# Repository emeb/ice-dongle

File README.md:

# ice-dongle
USB-C Dongle with ice40 UP5k FPGA

## Abstract
This is a small USB connected FPGA board in a "dongle" form-factor. Note that
it's not a true dongle since it doesn't have a USB plug (USB-C plugs are not
practical for DIY assembly at the time this was designed) - instead it has a
USB-C jack and you can use an inexpensive M-M adapter to achieve dongle-like
function.

For I/O it provides an 18-pin FPC connector that conforms to the Eye-SPI
standard found on some Adafruit products. This standard includes 3.3V power
as well as 16 GPIO for things like SPI or I2C device, most often TFT LCD
displays and user interfaces.

The FPGA is directly connected to USB and is pinned-out similarly to the
1bitsquared Icebreaker Bitsy so the NO2FPGA bootloader and user designs for
that ecosystem should port over with minimal changes. It includes 8MB of flash
and 8MB of PSRAM, as well as an RGB LED and a user button.

Initial programming of the FPGA bitstream takes place through a 1.27mm SMD
header footprint on the back of the board. The original intent was to access
this temporarily via the Adafruit "Pogo Pin Probe Clip" which should have
attached easily over the pads. Unfortunately the pogo pin row spacing is too
narrow for the SMT header pads so I ended up soldering on a header and using
a normal cable. This may be fixed in future revisions, but for now an actual
header + cable is probably more reliable for long-term development.

## Status
### 22-10-15
Boards are back from OSHpark and so far things are working.
* USB power, regulators and clock oscillator are running properly.
  * Minor silkscreen error was discovered - reference designators for R14 and C10 swapped.
* FPGA configures via programming header and from SPI flash.
* SPI flash can be written from the programming header.
* RGB LED works.
* EYESPI bus works with ST7789 TFT LCD
* PSRAM works.

### 22-10-16
USB FS interface is fully functional with the NO2 Bootloader. I've forked it to
add a custom BOARD target for ice-dongle but I'll submit a PR to the main project
when things settle down a bit. For the time being here's my fork:

[NO2 Bootloader](https://github.com/emeb/no2bootloader)

To build, clone that and follow the directions in the README. A few additional
notes:
* Don't forget to `git submodule update --init` to get all the related material
from the NO2 ecosystem.
* To build use `make BOARD=ice-dongle bootloader`
* The `riscv_lcd` gateware project has a `make dfu` target that shows how to use
the bootloader.

### 22-10-17
Ordered some helper boards to make interfacing easier:
* ice-fpc-pmod
* ice-prog-adapt

find out more about them in the [Hardware](Hardware) directory.

### 22-11-20
* Sylvain Munaut (@tnt) has built up a couple ice-dongle boards and confirmed that
they work outside my lab. He did spot another silkscreen error - R10 and C5 reference
designators are swapped. This doesn't significantly affect the board operation but
should be corrected.
* Updated NO2 board definition to put serial pins on programming
header and sent a PR which has been accepted. You can now use the mainline
NO2 bootloader repo instead of my fork.
* Added a LiteX gateware design. This works but even a minimal demo uses > 80% of
the FPGA resources.

### 22-11-21
Corrected silkscreen errors and bumped revision to V0.1a

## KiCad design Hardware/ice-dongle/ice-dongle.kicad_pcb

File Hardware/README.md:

# ice-dongle Hardware
These are kicad projects for the ice-dongle board.

## ice-dongle
the main board design for the ice-dongle

## ice-fpc-pmod
a simple FPC to dual PMOD breakout board. Note that this can be
used for both FPC -> PMOD socket as well as PMOD pin header -> FPC just by
flipping the board upside down.

## ice-prog-adapt
breaks out the 10-pin 1.27mm IDC header to 2.54mm single-row
pins for connection to a programmer and UART.

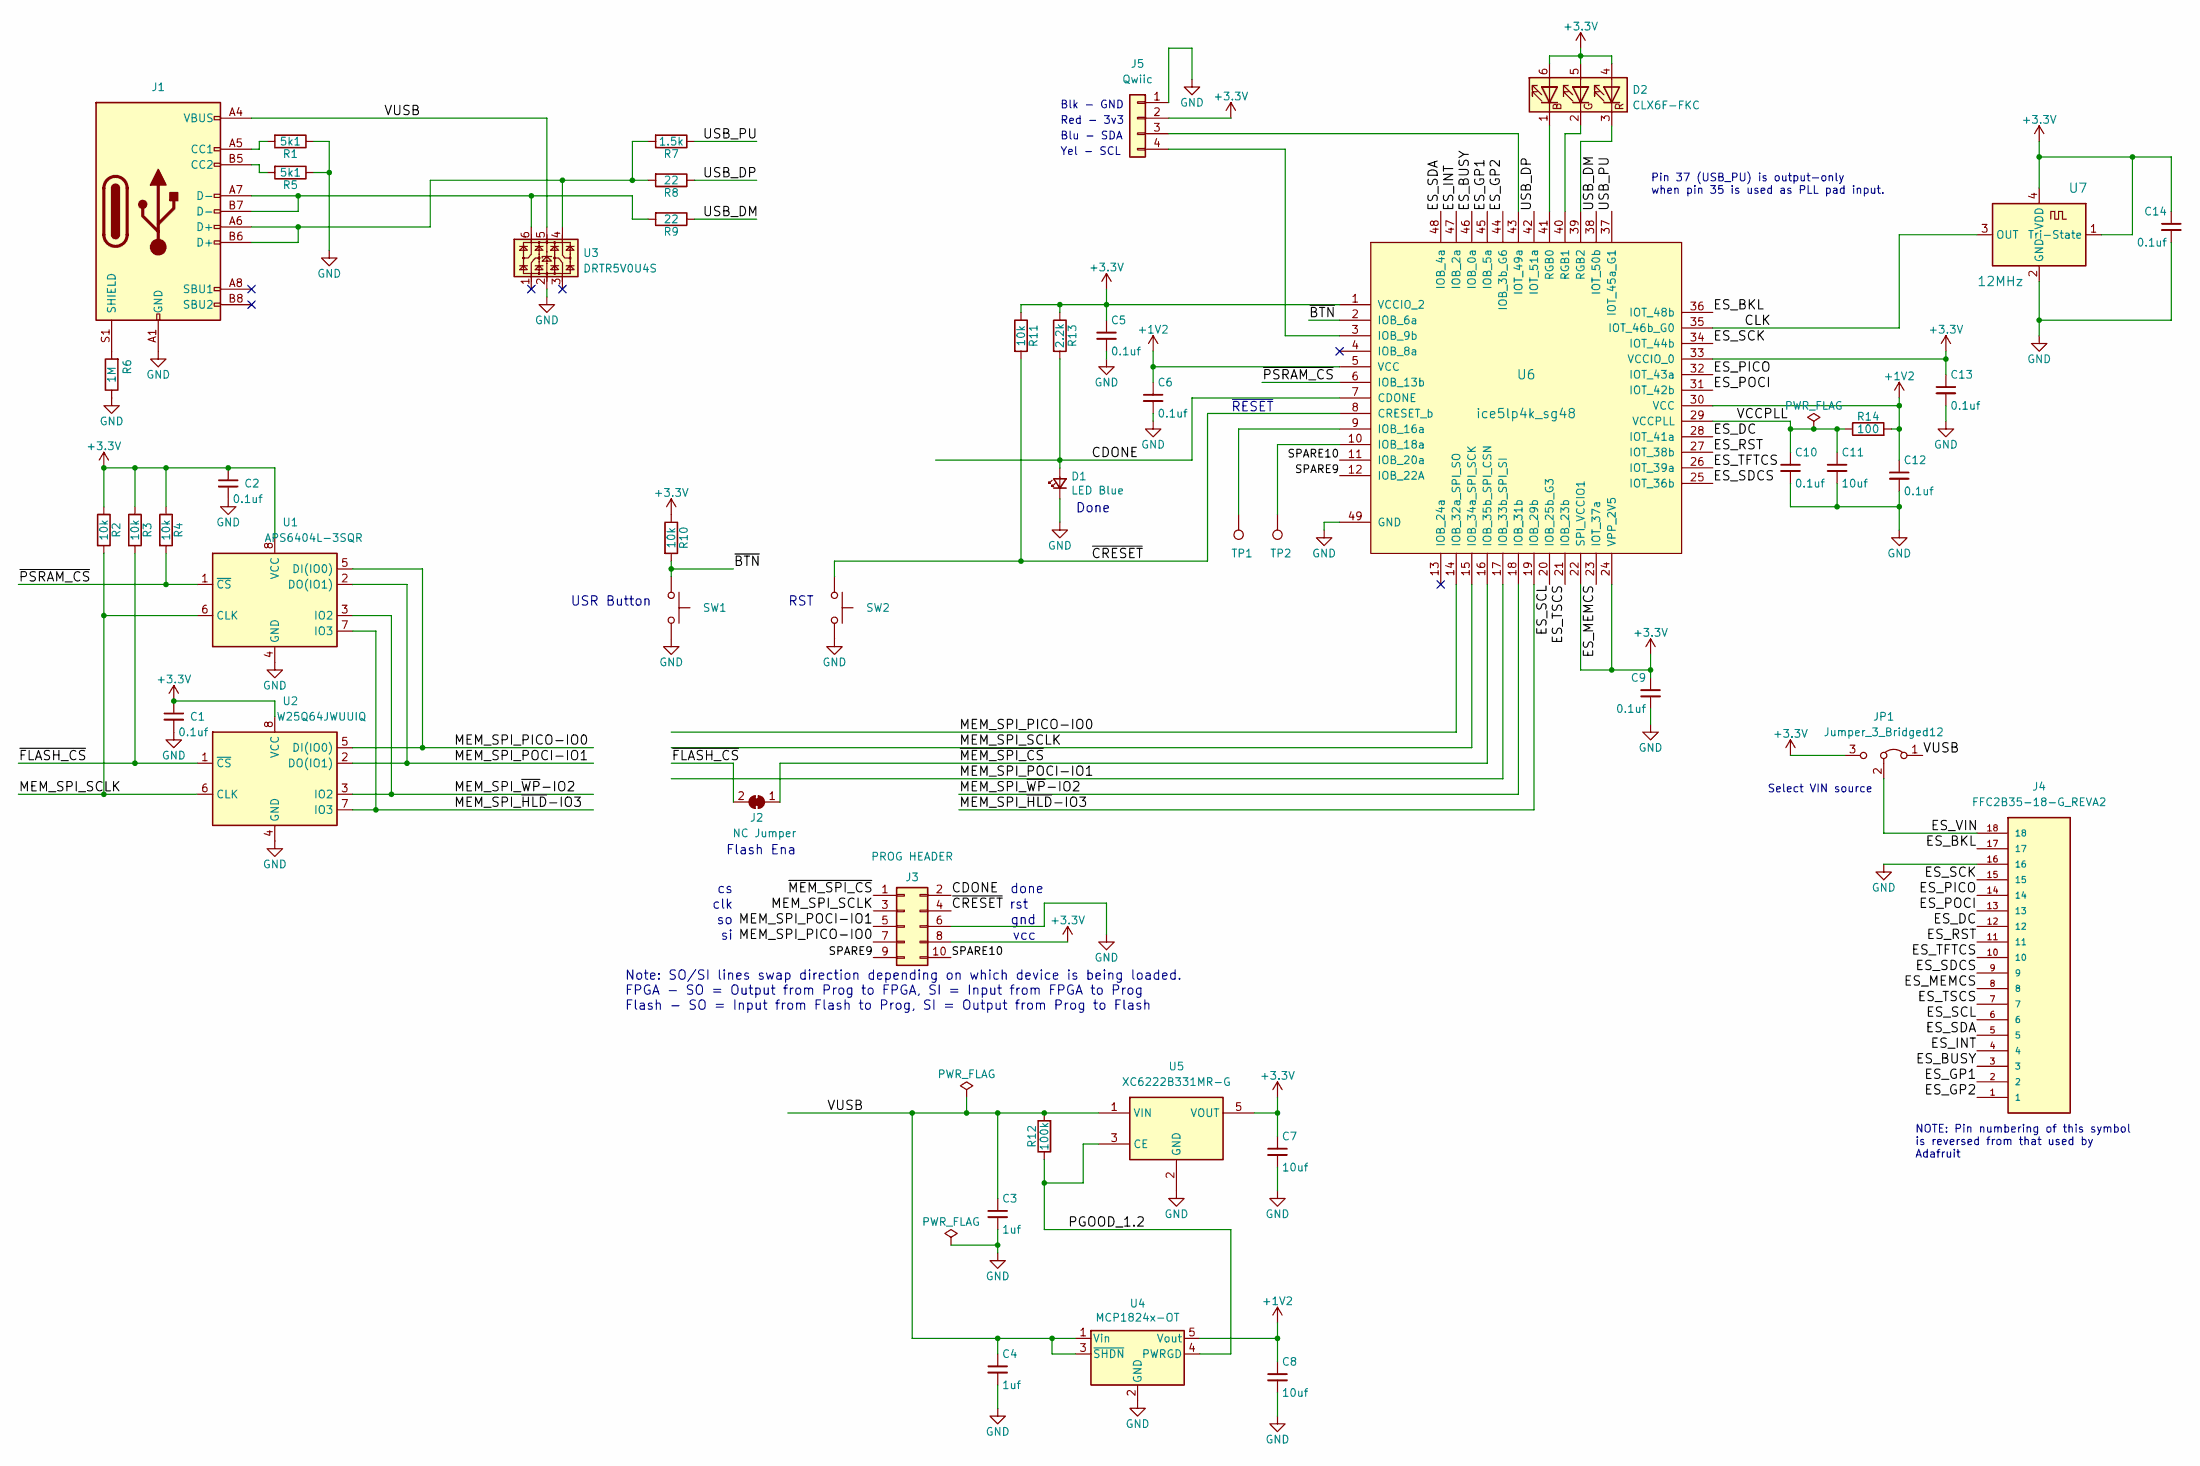
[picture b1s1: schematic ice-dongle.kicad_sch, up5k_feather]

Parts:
C1, C2, C5, C6, C9, C10, C12, C13, C14: 0.1uf; C_0402_1005Metric
C3, C4: 1uf; C_0402_1005Metric
C7, C8, C11: 10uf; C_0805_2012Metric
D1: LED Blue; LED_0603_1608Metric
D2: CLX6F-FKC; LED_RGB_PLCC-6
J1: USB_C_Receptacle_USB2.0; USB_C_Receptacle_HRO_TYPE-C-31-M-12
J2: NC Jumper; SolderJumper-2_P1.3mm_Bridged_RoundedPad1.0x1.5mm
J3: PROG HEADER; PinHeader_2x05_P1.27mm_Vertical_SMD
J4: FFC2B35-18-G_REVA2; GCT_FFC2B35-18-G_REVA2; PARTREV A2
J5: Qwiic; PinHeader_1x04_P1.27mm_Vertical
JP1: Jumper_3_Bridged12; SolderJumper-3_P1.3mm_Bridged12_RoundedPad1.0x1.5mm
R1, R5: 5k1; R_0402_1005Metric
R2, R3, R4, R10, R11: 10k; R_0402_1005Metric
R6: 1M; R_0402_1005Metric
R7: 1.5k; R_0402_1005Metric
R8, R9: 22; R_0402_1005Metric
R12: 100k; R_0402_1005Metric
R13: 2.2k; R_0402_1005Metric
R14: 100; R_0402_1005Metric
SW1, SW2: SW_Push; SW_SPST_PTS815
TP1, TP2: TestPoint; TestPoint_Pad_D0.5mm
U1: APS6404L-3SQR; USON-8_2x3
U2: W25Q64JWUUIQ; USON-8_4x3
U3: DRTR5V0U4S; SOT-363_SC-70-6
U4: MCP1824x-OT; SOT-23-5
U5: XC6222B331MR-G; SOT-23-5
U6: ice5lp4k_sg48; QFN-48-1EP_7x7mm_P0.5mm_EP5.3x5.3mm
U7: 12MHz; Oscillator_SMD_ECS_2520MV-xxx-xx-4Pin_2.5x2.0mm

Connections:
+1V2: C6.1, C8.1, C12.1, R14.2, U4.5 (Vout), U6.5 (VCC), U6.30 (VCC)
+3.3V: C1.1, C2.1, C5.1, C7.1, C9.1, C13.1, C14.1, D2.4 (BA), D2.5 (GA), D2.6 (RA), J3.8, J5.2, JP1.3 (B), R2.1, R3.1, R4.1, R10.1, R11.1, R13.1, U1.8 (VCC), U2.8 (VCC), U5.5 (VOUT), U6.1 (VCCIO_2), U6.22 (SPI_VCCIO1), U6.24 (VPP_2V5), U6.33 (VCCIO_0), U7.1 (Tri-State), U7.4 (VDD)
/CDONE: D1.2 (A), J3.2, R13.2, U6.7 (CDONE)
/CLK: U6.35 (IOT_46b_G0), U7.3 (OUT)
/ES_BKL: J4.17, U6.36 (IOT_48b)
/ES_BUSY: J4.3, U6.46 (IOB_0a)
/ES_DC: J4.12, U6.28 (IOT_41a)
/ES_GP1: J4.2, U6.45 (IOB_5a)
/ES_GP2: J4.1, U6.44 (IOB_3b_G6)
/ES_INT: J4.4, U6.47 (IOB_2a)
/ES_MEMCS: J4.8, U6.23 (IOT_37a)
/ES_PICO: J4.14, U6.32 (IOT_43a)
/ES_POCI: J4.13, U6.31 (IOT_42b)
/ES_RST: J4.11, U6.27 (IOT_38b)
/ES_SCK: J4.15, U6.34 (IOT_44b)
/ES_SCL: J4.6, U6.20 (IOB_25b_G3)
/ES_SDA: J4.5, U6.48 (IOB_4a)
/ES_SDCS: J4.9, U6.25 (IOT_36b)
/ES_TFTCS: J4.10, U6.26 (IOT_39a)
/ES_TSCS: J4.7, U6.21 (IOB_23b)
/ES_VIN: J4.18, JP1.2 (C)
/MEM_SPI_PICO-IO0: J3.7, U1.5 (DI(IO0)), U2.5 (DI(IO0)), U6.14 (IOB_32a_SPI_SO)
/MEM_SPI_POCI-IO1: J3.5, U1.2 (DO(IO1)), U2.2 (DO(IO1)), U6.17 (IOB_33b_SPI_SI)
/MEM_SPI_SCLK: J3.3, R2.2, U1.6 (CLK), U2.6 (CLK), U6.15 (IOB_34a_SPI_SCK)
/MEM_SPI_~HLD-IO3: U1.7 (IO3), U2.7 (IO3), U6.19 (IOB_29b)
/MEM_SPI_~WP-IO2: U1.3 (IO2), U2.3 (IO2), U6.18 (IOB_31b)
/PGOOD_1.2: R12.1, U4.4 (PWRGD), U5.3 (CE)
/SPARE9: J3.9, U6.12 (IOB_22A)
/SPARE10: J3.10, U6.11 (IOB_20a)
/USB_DM: R9.1, U6.38 (IOT_50b)
/USB_DP: R8.1, U6.42 (IOT_51a)
/USB_PU: R7.1, U6.37 (IOT_45a_G1)
/VCCPLL: C10.1, C11.1, R14.1, U6.29 (VCCPLL)
/VUSB: C3.1, C4.1, J1.A4 (VBUS), J1.A9 (VBUS), J1.B4 (VBUS), J1.B9 (VBUS), JP1.1 (A), R12.2, U3.5, U4.1 (Vin), U4.3 (~SHDN), U5.1 (VIN)
/~BTN: R10.2, SW1.1, U6.2 (IOB_6a)
/~CRESET: J3.4, R11.2, SW2.1, U6.8 (CRESET_b)
/~FLASH_CS: J2.2 (B), R3.2, U2.1 (~CS)
/~MEM_SPI_CS: J2.1 (A), J3.1, U6.16 (IOB_35b_SPI_CSN)
/~PSRAM_CS: R4.2, U1.1 (~CS), U6.6 (IOB_13b)
GND: C1.2, C2.2, C3.2, C4.2, C5.2, C6.2, C7.2, C8.2, C9.2, C10.2, C11.2, C12.2, C13.2, C14.2, D1.1 (K), J1.A1 (GND), J1.A12 (GND), J1.B1 (GND), J1.B12 (GND), J3.6, J4.16, J5.1, R1.1, R5.1, R6.1, SW1.2, SW2.2, U1.4 (GND), U2.4 (GND), U3.2, U4.2 (GND), U5.2 (GND), U6.49 (GND), U7.2 (GND)
unnamed: D2.1 (RK), U6.41 (RGB0)
unnamed: D2.2 (GK), U6.40 (RGB1)
unnamed: D2.3 (BK), U6.39 (RGB2)
unnamed: J1.A5 (CC1), R1.2
unnamed: J1.A6 (D+), J1.B6 (D+), R7.2, R8.2, U3.4
unnamed: J1.A7 (D-), J1.B7 (D-), R9.2, U3.6
unnamed: J1.B5 (CC2), R5.2
unnamed: J1.S1 (SHIELD), R6.2
unnamed: J5.3, U6.43 (IOT_49a)
unnamed: J5.4, U6.3 (IOB_9b)
unnamed: TP1.1, U6.9 (IOB_16a)
unnamed: TP2.1, U6.10 (IOB_18a)

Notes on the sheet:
vcc
done
Yel - SCL
RST
Blk - GND
USR Button
Red - 3v3
Note: SO/SI lines swap direction depending on which device is being loaded. FPGA - SO = Output from Prog to FPGA, SI = Input from FPGA to Prog Flash - SO = Input from Flash to Prog, SI = Output from Prog to Flash
Done
gnd
Flash Ena
clk
Pin 37 (USB_PU) is output-only when pin 35 is used as PLL pad input.
NOTE: Pin numbering of this symbol is reversed from that used by Adafruit
Blu - SDA
rst
~{RESET}
Select VIN source

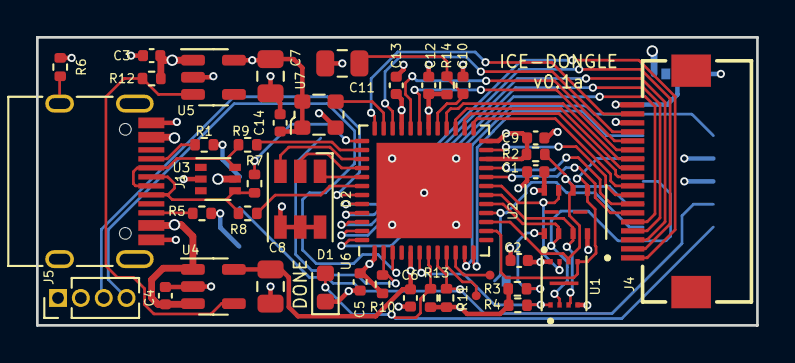
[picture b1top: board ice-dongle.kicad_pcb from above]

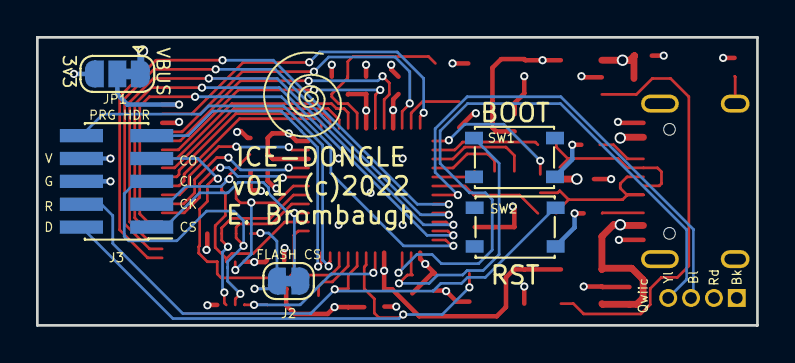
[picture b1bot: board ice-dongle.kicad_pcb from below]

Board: 4 copper layers, 40.0 x 16.0 mm, 48 parts (6 on the bottom side), 52 nets.

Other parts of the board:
Ref**: Val**; avatar_small

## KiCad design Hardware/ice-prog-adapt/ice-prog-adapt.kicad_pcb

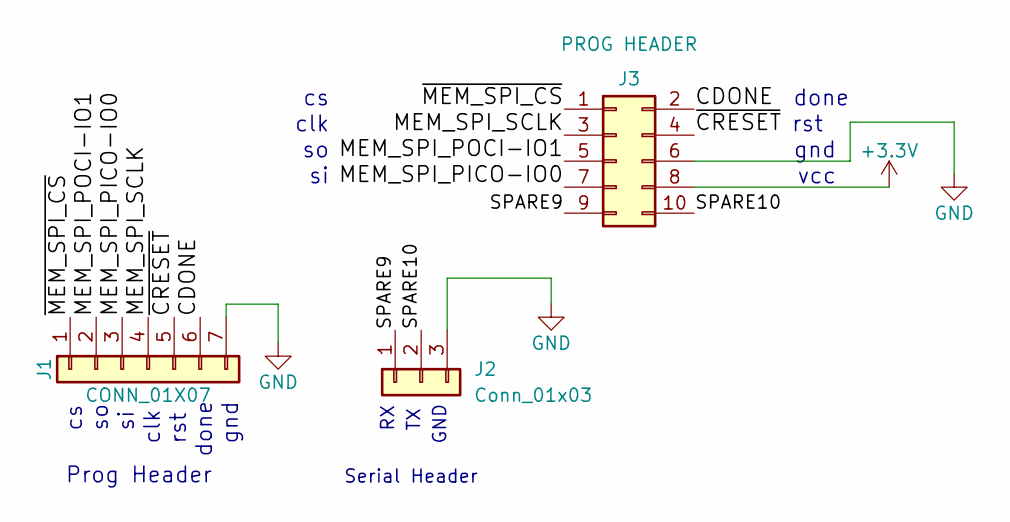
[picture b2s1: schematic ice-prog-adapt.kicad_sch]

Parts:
J1: CONN_01X07; PinHeader_1x07_P2.54mm_Vertical
J2: Conn_01x03; PinHeader_1x03_P2.54mm_Vertical
J3: PROG HEADER; PinHeader_2x05_P1.27mm_Vertical_SMD

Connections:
+3.3V: J3.8
/CDONE: J1.6, J3.2
/MEM_SPI_PICO-IO0: J1.3, J3.7
/MEM_SPI_POCI-IO1: J1.2, J3.5
/MEM_SPI_SCLK: J1.4, J3.3
/SPARE9: J2.1, J3.9
/SPARE10: J2.2, J3.10
/~CRESET: J1.5, J3.4
/~MEM_SPI_CS: J1.1, J3.1
GND: J1.7, J2.3, J3.6

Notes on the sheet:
GND
Serial Header
vcc
gnd
clk
done
rst
Prog Header

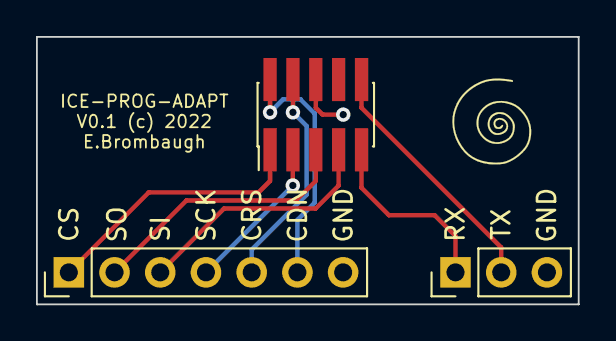
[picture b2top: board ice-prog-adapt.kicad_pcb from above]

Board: 2 copper layers, 30.1 x 14.9 mm, 4 parts (0 on the bottom side), 9 nets.

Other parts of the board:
Ref**: Val**; avatar_small

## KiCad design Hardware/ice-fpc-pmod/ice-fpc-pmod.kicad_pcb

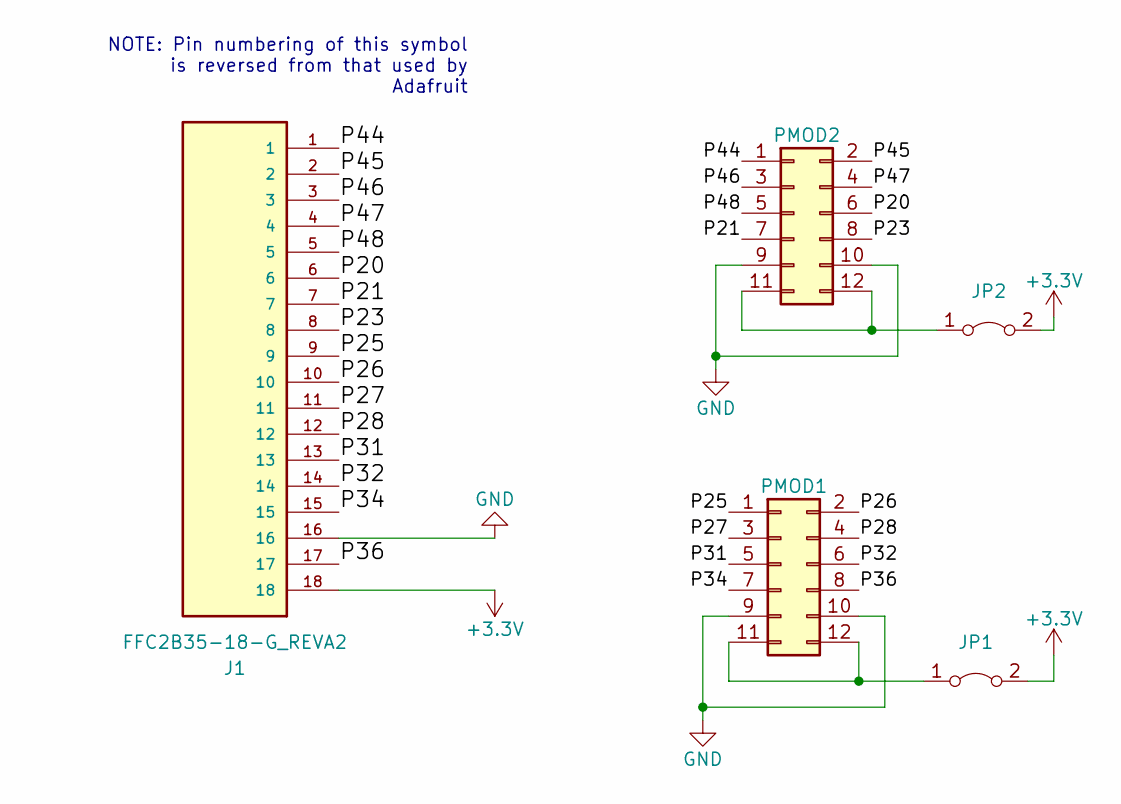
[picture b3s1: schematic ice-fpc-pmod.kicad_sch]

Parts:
J1: FFC2B35-18-G_REVA2; GCT_FFC2B35-18-G_REVA2; PARTREV A2
JP1, JP2: Jumper_2_Bridged; SolderJumper-2_P1.3mm_Bridged_RoundedPad1.0x1.5mm
PMOD1, PMOD2: CONN_02X06; PinSocket_2x06_P2.54mm_Vertical

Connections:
+3.3V: J1.18, JP1.2 (B), JP2.2 (B)
/P20: J1.6, PMOD2.6
/P21: J1.7, PMOD2.7
/P23: J1.8, PMOD2.8
/P25: J1.9, PMOD1.1
/P26: J1.10, PMOD1.2
/P27: J1.11, PMOD1.3
/P28: J1.12, PMOD1.4
/P31: J1.13, PMOD1.5
/P32: J1.14, PMOD1.6
/P34: J1.15, PMOD1.7
/P36: J1.17, PMOD1.8
/P44: J1.1, PMOD2.1
/P45: J1.2, PMOD2.2
/P46: J1.3, PMOD2.3
/P47: J1.4, PMOD2.4
/P48: J1.5, PMOD2.5
GND: J1.16, PMOD1.9, PMOD1.10, PMOD2.9, PMOD2.10
unnamed: JP1.1 (A), PMOD1.11, PMOD1.12
unnamed: JP2.1 (A), PMOD2.11, PMOD2.12

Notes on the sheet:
NOTE: Pin numbering of this symbol is reversed from that used by Adafruit

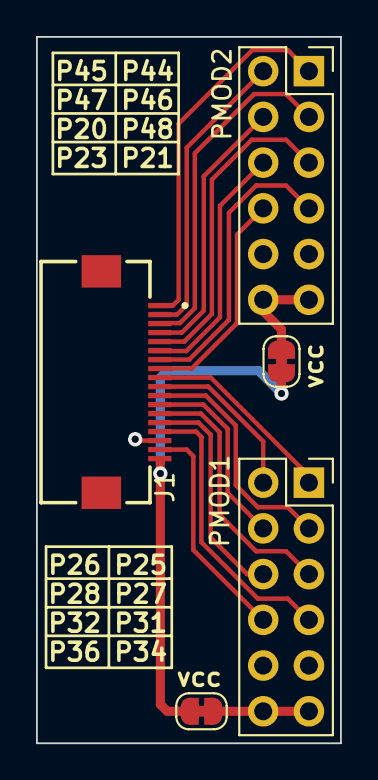
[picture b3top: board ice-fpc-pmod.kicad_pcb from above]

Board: 2 copper layers, 16.9 x 39.2 mm, 6 parts (1 on the bottom side), 20 nets.

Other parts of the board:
Ref**: Val**; avatar_small

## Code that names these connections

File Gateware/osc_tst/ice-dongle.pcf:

######################
# ice-dongle pinout
######################

# Boot Button
set_io BTN 2

# StemmaQT / QWIIC 
set_io QWIIC_SCL 3
set_io QWIIC_SDA 43

# Spares on Programming Header
set_io SPARE9 12
set_io SPARE10 11

# testpoints
set_io TP1 9
set_io TP2 10

# NC pins
set_io NC4 4
set_io NC13 13

# SPI Memory interface
set_io MEM_SPI_PICO_IO0 14
set_io MEM_SPI_POCI_IO1 17
set_io MEM_SPI_SCLK 15
set_io MEM_SPI_CS 16
set_io MEM_SPI_WP_IO2 18
set_io MEM_SPI_HLD_IO3 19
set_io PSRAM_CS 6

# Eye-SPI connector
set_io ES_BKL 36
set_io ES_SCK 34
set_io ES_PICO 32
set_io ES_POCI 31
set_io ES_DC 28
set_io ES_RST 27
set_io ES_TFTCS 26
set_io ES_SDCS 25
set_io ES_MEMCS 23
set_io ES_TSCS 21
set_io ES_SCL 20
set_io ES_SDA 48
set_io ES_INT 47
set_io ES_BUSY 46
set_io ES_GP1 45
set_io ES_GP2 44

# USB
set_io USB_DP 42
set_io USB_DM 38
set_io USB_PU 37

# 12MHz Clock Oscillator
set_io CLK12MHZ 35

# RGB LED
set_io RGB0 39
set_io RGB1 40
set_io RGB2 41

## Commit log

2022-09-21 Initial commit of ice-dongle project
2022-09-25 USB-C jack, finish layout
2022-09-25 Added image to README
2022-09-25 Fix Eye-SPI pinout, add VIN selector
2022-09-25 Update image
2022-09-25 Fix issues pointed out by @m_w, update image
2022-09-25 Clean up USB & RGB routing.
2022-09-26 Added
2022-09-26 Minor cleanups, add unmarked testpoints to unused IO
2022-10-16 Updated w/ new status
2022-10-16 Added Gateware to repo
2022-10-16 Added READMEs for gateware
2022-10-16 Added image display from SPI flash
2022-10-16 Tested USB and Added NO2 Bootloader support
2022-10-16 updated info on header programming.
2022-10-17 LED dimming, put image into DFU region 1
2022-10-19 Added some supporting board designs
2022-10-19 Add some thumbnails
2022-10-27 Update docs
2022-10-27 formatting
2022-11-11 move serial pins to programming header
2022-11-12 Serial echo and non-blocking LED timing
2022-11-13 Working to add command interp
2022-11-19 Working on command interpreter
2022-11-20 Working on litex builds
2022-11-20 Working. Added README with instructions.
2022-11-20 Update README with latest news.
2022-11-22 Corrected swapped silkscreen refdes, bumped version to 0.1a
2022-11-22 Updated README for PCB fixes.
2022-12-07 Adding 6502 project
2022-12-07 fixing submodule mess
2022-12-07 Adding external 6502 IP core
2022-12-07 Fix serial rate
2022-12-09 Added no2 muacm + 6502 monitor project
2022-12-10 Added 6502 ROM building
2022-12-10 Added 52kB SPRAM and rearranged I/O to support BASIC
2022-12-10 Added SPI port for reading flash
2022-12-11 MS BASIC works now
2022-12-13 Added PSRAM chip select, working on routines for flexible CS
2023-03-08 Added microsecond timer and fixed USB RX interlock
2023-03-09 Added RGB IP core, tool path to makefile
2023-03-09 Added demo programs
2023-03-09 Use latest oss cad suite, fix load/save address to prevent damaging bootloader

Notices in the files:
Hardware/ice-dongle/ice-dongle.kicad_pcb:
v0.1 (c)2022
